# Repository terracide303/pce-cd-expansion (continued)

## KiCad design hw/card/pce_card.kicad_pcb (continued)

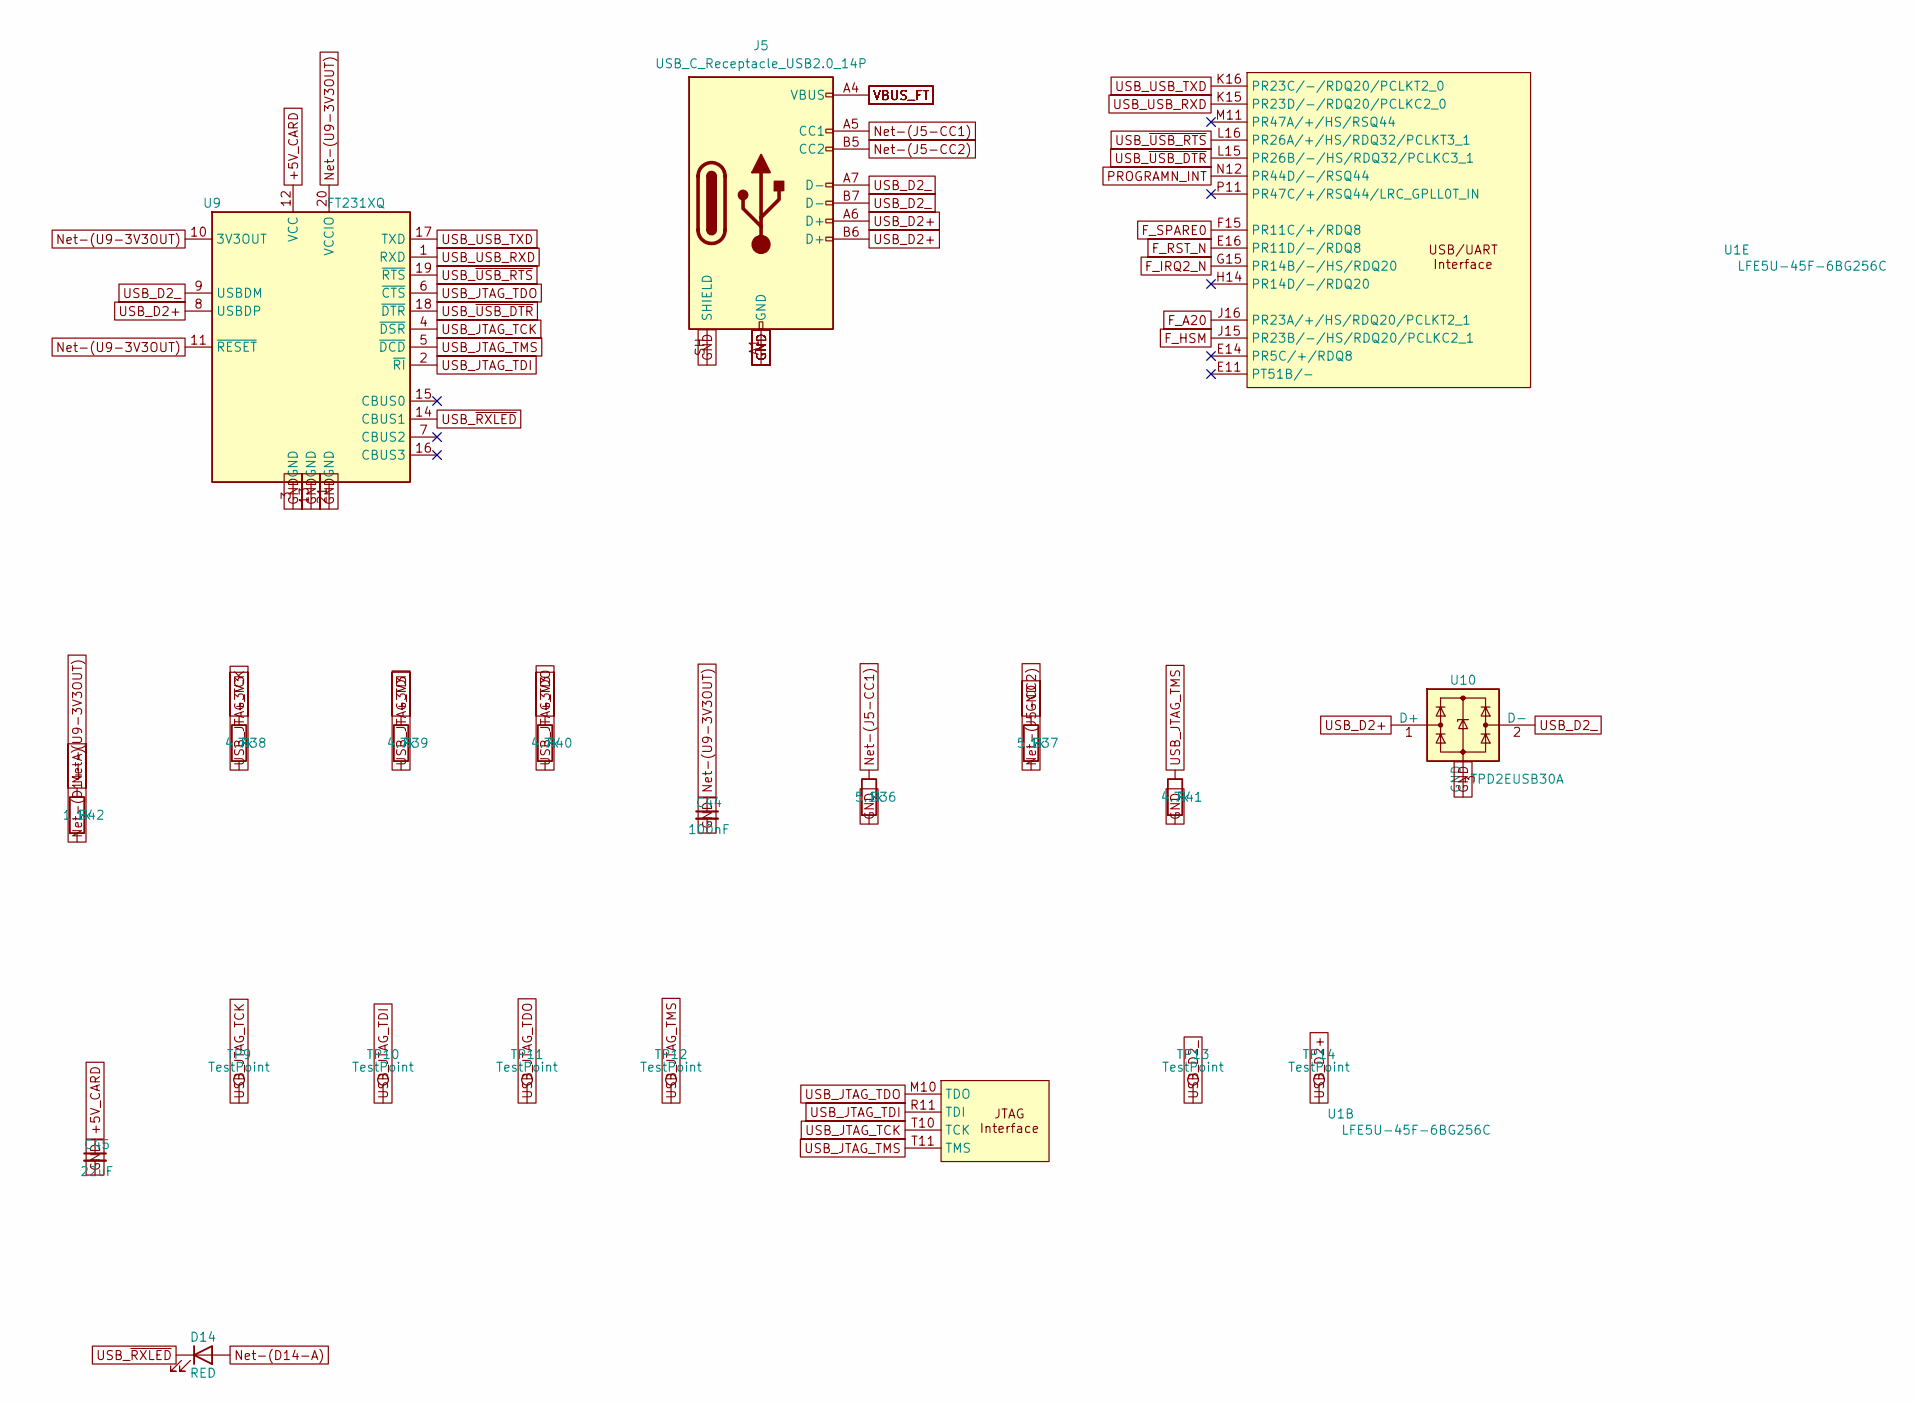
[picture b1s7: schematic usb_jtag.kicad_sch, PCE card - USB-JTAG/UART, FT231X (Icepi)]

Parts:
C44: 100nF; C_0402_1005Metric; LCSC C307331
C45: 22uF; C_0603_1608Metric; LCSC C59461
D14: RED; LED_0603_1608Metric; LCSC C2286
J5: USB_C_Receptacle_USB2.0_14P; USB_C_Receptacle_GCT_USB4105-xx-A_16P_TopMnt_Horizontal; LCSC C2765186
R36, R37: 5.1k; R_0402_1005Metric; LCSC C25905
R38, R39, R40, R41: 4.7k; R_0402_1005Metric; LCSC C25900
R42: 1.1k; R_0402_1005Metric; LCSC C140223
TP9, TP10, TP11, TP12: TestPoint; TestPoint_Pad_D1.0mm_Blank
TP13, TP14: TestPoint; TestPoint_Pad_D2.0mm_Blank
U1: LFE5U-45F-6BG256C; BGA-256_14.0x14.0mm_Layout16x16_P0.8mm_Ball0.45mm_Pad0.32mm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; LCSC C1550834
U9: FT231XQ; QFN-20-1EP_4x4mm_P0.5mm_EP2.5x2.5mm; LCSC C132159
U10: TPD2EUSB30A; Texas_DRT-3; LCSC C3011197

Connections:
+3V3: R38.1, R39.1, R40.1; also elsewhere on the board
+5V_CARD: C45.1, U9.12 (VCC); also elsewhere on the board
F_A20: U1.J16 (PR23A/+/HS/RDQ20/PCLKT2_1); also elsewhere on the board
F_HSM: U1.J15 (PR23B/-/HS/RDQ20/PCLKC2_1); also elsewhere on the board
F_IRQ2_N: U1.G15 (PR14B/-/HS/RDQ20); also elsewhere on the board
F_RST_N: U1.E16 (PR11D/-/RDQ8); also elsewhere on the board
F_SPARE0: U1.F15 (PR11C/+/RDQ8); also elsewhere on the board
GND: C44.2, C45.2, J5.A1 (GND), J5.A12 (GND), J5.B1 (GND), J5.B12 (GND), J5.SH (SHIELD), R36.2, R37.1, R41.2, U9.3 (GND), U9.13 (GND), U9.21 (GND), U10.3 (GND); also elsewhere on the board
unnamed: D14.2 (A), R42.2
unnamed: J5.A5 (CC1), R36.1
unnamed: J5.B5 (CC2), R37.2
unnamed: C44.1, R42.1, U9.10 (3V3OUT), U9.11 (~RESET), U9.20 (VCCIO)
PROGRAMN_INT: U1.N12 (PR44D/-/RSQ44); also elsewhere on the board
USB_D2+: J5.A6 (D+), J5.B6 (D+), TP14.1, U9.8 (USBDP), U10.1 (D+)
USB_D2_: J5.A7 (D-), J5.B7 (D-), TP13.1, U9.9 (USBDM), U10.2 (D-)
USB_JTAG_TCK: R38.2, TP9.1, U1.T10 (TCK), U9.4 (~DSR)
USB_JTAG_TDI: R39.2, TP10.1, U1.R11 (TDI), U9.2 (~RI)
USB_JTAG_TDO: R40.2, TP11.1, U1.M10 (TDO), U9.6 (~CTS)
USB_JTAG_TMS: R41.1, TP12.1, U1.T11 (TMS), U9.5 (~DCD)
USB_USB_RXD: U1.K15 (PR23D/-/RDQ20/PCLKC2_0), U9.1 (RXD)
USB_USB_TXD: U1.K16 (PR23C/-/RDQ20/PCLKT2_0), U9.17 (TXD)
USB_~RXLED: D14.1 (K), U9.14 (CBUS1)
USB_~USB_DTR: U1.L15 (PR26B/-/HS/RDQ32/PCLKC3_1), U9.18 (~DTR)
USB_~USB_RTS: U1.L16 (PR26A/+/HS/RDQ32/PCLKT3_1), U9.19 (~RTS)
VBUS_FT: J5.A4 (VBUS), J5.A9 (VBUS), J5.B4 (VBUS), J5.B9 (VBUS); also elsewhere on the board

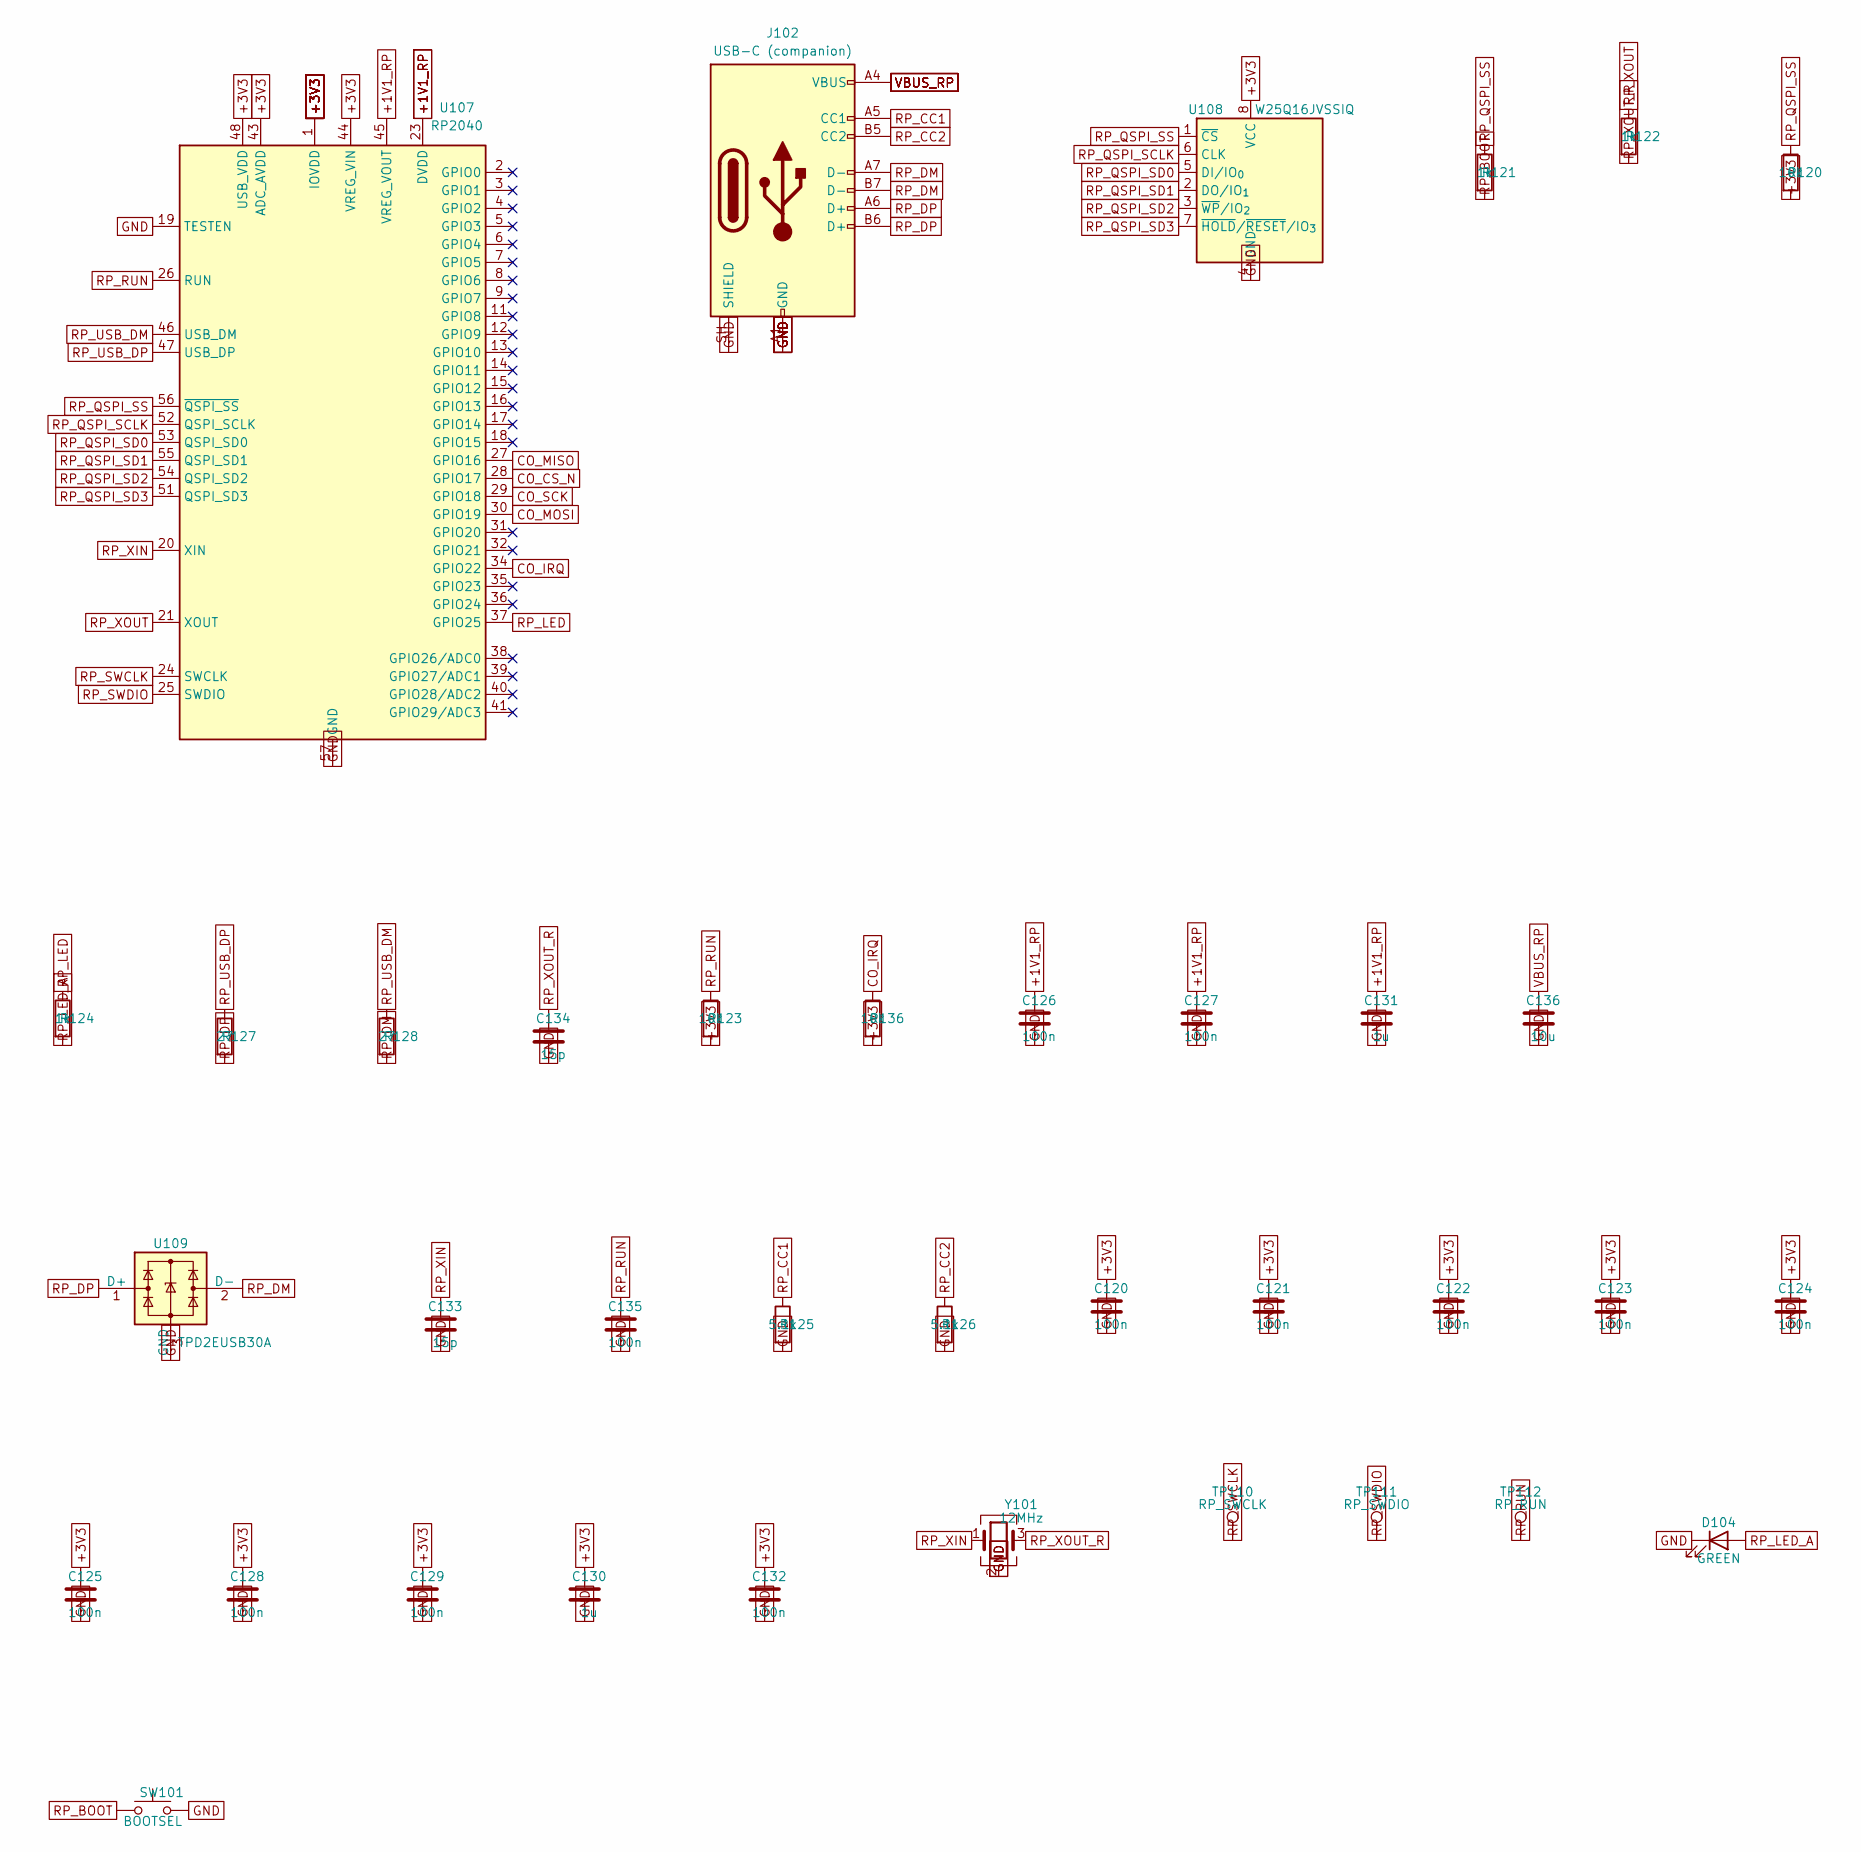
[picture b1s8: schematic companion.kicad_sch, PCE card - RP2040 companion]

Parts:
C120, C121, C122, C123, C124, C125, C126, C127, C128, C129, C132, C135: 100n; C_0402_1005Metric; LCSC C307331
C130, C131: 1u; C_0402_1005Metric
C133, C134: 15p; C_0402_1005Metric
C136: 10u; C_0603_1608Metric; LCSC C19702
D104: GREEN; LED_0603_1608Metric
J102: USB-C (companion); USB_C_Receptacle_GCT_USB4105-xx-A_16P_TopMnt_Horizontal; LCSC C2765186
R120, R123, R136: 10k; R_0402_1005Metric; LCSC C25744
R121, R122, R124: 1k; R_0402_1005Metric
R125, R126: 5.1k; R_0402_1005Metric; LCSC C25905
R127, R128: 27; R_0402_1005Metric
SW101: BOOTSEL; switch_button_TS-1088-AR02016; LCSC C720477
TP110: RP_SWCLK; TestPoint_Pad_D1.0mm
TP111: RP_SWDIO; TestPoint_Pad_D1.0mm
TP112: RP_RUN; TestPoint_Pad_D1.0mm
U107: RP2040; QFN-56-1EP_7x7mm_P0.4mm_EP3.2x3.2mm; LCSC C2040
U108: W25Q16JVSSIQ; SOIC-8_5.3x5.3mm_P1.27mm
U109: TPD2EUSB30A; Texas_DRT-3; LCSC C3011197
Y101: 12MHz; Crystal_SMD_3225-4Pin_3.2x2.5mm

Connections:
+1V1_RP: C126.1, C127.1, C131.1, U107.23 (DVDD), U107.45 (VREG_VOUT), U107.50 (DVDD)
+3V3: C120.1, C121.1, C122.1, C123.1, C124.1, C125.1, C128.1, C129.1, C130.1, C132.1, R120.2, R123.2, R136.2, U107.1 (IOVDD), U107.10 (IOVDD), U107.22 (IOVDD), U107.33 (IOVDD), U107.42 (IOVDD), U107.43 (ADC_AVDD), U107.44 (VREG_VIN), U107.48 (USB_VDD), U107.49 (IOVDD), U108.8 (VCC); also elsewhere on the board
CO_CS_N: U107.28 (GPIO17); also elsewhere on the board
CO_IRQ: R136.1, U107.34 (GPIO22); also elsewhere on the board
CO_MISO: U107.27 (GPIO16); also elsewhere on the board
CO_MOSI: U107.30 (GPIO19); also elsewhere on the board
CO_SCK: U107.29 (GPIO18); also elsewhere on the board
GND: C120.2, C121.2, C122.2, C123.2, C124.2, C125.2, C126.2, C127.2, C128.2, C129.2, C130.2, C131.2, C132.2, C133.2, C134.2, C135.2, C136.2, D104.1 (K), J102.A1 (GND), J102.A12 (GND), J102.B1 (GND), J102.B12 (GND), J102.SH (SHIELD), R125.2, R126.2, SW101.2, U107.19 (TESTEN), U107.57 (GND), U108.4 (GND), U109.3 (GND), Y101.2 (G), Y101.4 (G); also elsewhere on the board
RP_BOOT: R121.2, SW101.1
RP_CC1: J102.A5 (CC1), R125.1
RP_CC2: J102.B5 (CC2), R126.1
RP_DM: J102.A7 (D-), J102.B7 (D-), R128.2, U109.2 (D-)
RP_DP: J102.A6 (D+), J102.B6 (D+), R127.2, U109.1 (D+)
RP_LED: R124.1, U107.37 (GPIO25)
RP_LED_A: D104.2 (A), R124.2
RP_QSPI_SCLK: U107.52 (QSPI_SCLK), U108.6 (CLK)
RP_QSPI_SD0: U107.53 (QSPI_SD0), U108.5 (DI/IO_{0})
RP_QSPI_SD1: U107.55 (QSPI_SD1), U108.2 (DO/IO_{1})
RP_QSPI_SD2: U107.54 (QSPI_SD2), U108.3 (~WP/IO_{2})
RP_QSPI_SD3: U107.51 (QSPI_SD3), U108.7 (~HOLD/~RESET/IO_{3})
RP_QSPI_SS: R120.1, R121.1, U107.56 (~QSPI_SS), U108.1 (~CS)
RP_RUN: C135.1, R123.1, TP112.1, U107.26 (RUN)
RP_SWCLK: TP110.1, U107.24 (SWCLK)
RP_SWDIO: TP111.1, U107.25 (SWDIO)
RP_USB_DM: R128.1, U107.46 (USB_DM)
RP_USB_DP: R127.1, U107.47 (USB_DP)
RP_XIN: C133.1, U107.20 (XIN), Y101.1
RP_XOUT: R122.1, U107.21 (XOUT)
RP_XOUT_R: C134.1, R122.2, Y101.3
VBUS_RP: C136.1, J102.A4 (VBUS), J102.A9 (VBUS), J102.B4 (VBUS), J102.B9 (VBUS); also elsewhere on the board

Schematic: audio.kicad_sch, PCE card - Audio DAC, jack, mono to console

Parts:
C140, C141: 2.2u; C_0603_1608Metric
C142: 1u; C_0402_1005Metric
C143, C144, C145: 100n; C_0402_1005Metric; LCSC C307331
C146, C149, C150, C151: 10u; C_0603_1608Metric; LCSC C19702
C147, C148: 2.2n; C_0402_1005Metric
J103: 3.5 mm stereo; Jack_3.5mm_CUI_SJ-3523-SMT_Horizontal
R130, R134, R135: 10k; R_0402_1005Metric; LCSC C25744
R131, R132: 470; R_0402_1005Metric; LCSC C25117
R133: 4.7k; R_0402_1005Metric; LCSC C25900
U110: PCM5102APWR; TSSOP-20_4.4x6.5mm_P0.65mm

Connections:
+3V3: C143.1, C144.1, C145.1, C146.1, C150.1, C151.1, R130.2, U110.1 (CPVDD), U110.8 (AVDD), U110.20 (DVDD); also elsewhere on the board
AUD_L: C147.1, J103.T, R131.2, R134.1
AUD_MIX: C149.1, R133.1, R134.2, R135.2
AUD_R: C148.1, J103.R, R132.2, R135.1
BUS_AUDIO: C149.2; also elsewhere on the board
DAC_CAPM: C140.2, U110.4 (CAPM)
DAC_CAPP: C140.1, U110.2 (CAPP)
DAC_LDOO: C142.1, U110.18 (LDOO)
DAC_OUTL: R131.1, U110.6 (OUTL)
DAC_OUTR: R132.1, U110.7 (OUTR)
DAC_VNEG: C141.1, U110.5 (VNEG)
DAC_XSMT: R130.1, U110.17 (XSMT)
F_I2S_BCK: U110.13 (BCK); also elsewhere on the board
F_I2S_DIN: U110.14 (DIN); also elsewhere on the board
F_I2S_LRCK: U110.15 (LRCK); also elsewhere on the board
GND: C141.2, C142.2, C143.2, C144.2, C145.2, C146.2, C147.2, C148.2, C150.2, C151.2, J103.S, R133.2, U110.3 (CPGND), U110.9 (AGND), U110.10 (DEMP), U110.11 (FLT), U110.12 (SCK), U110.16 (FMT), U110.19 (DGND); also elsewhere on the board

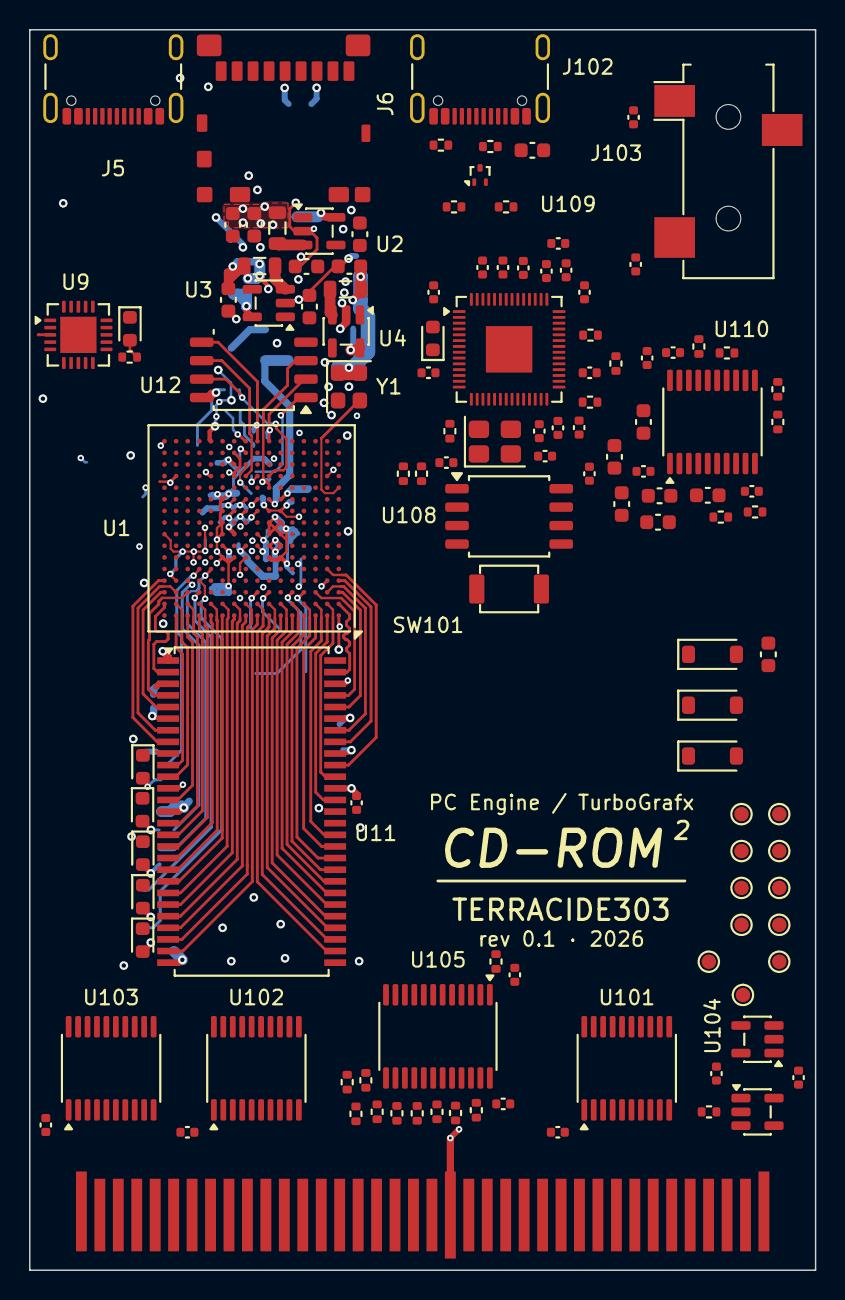
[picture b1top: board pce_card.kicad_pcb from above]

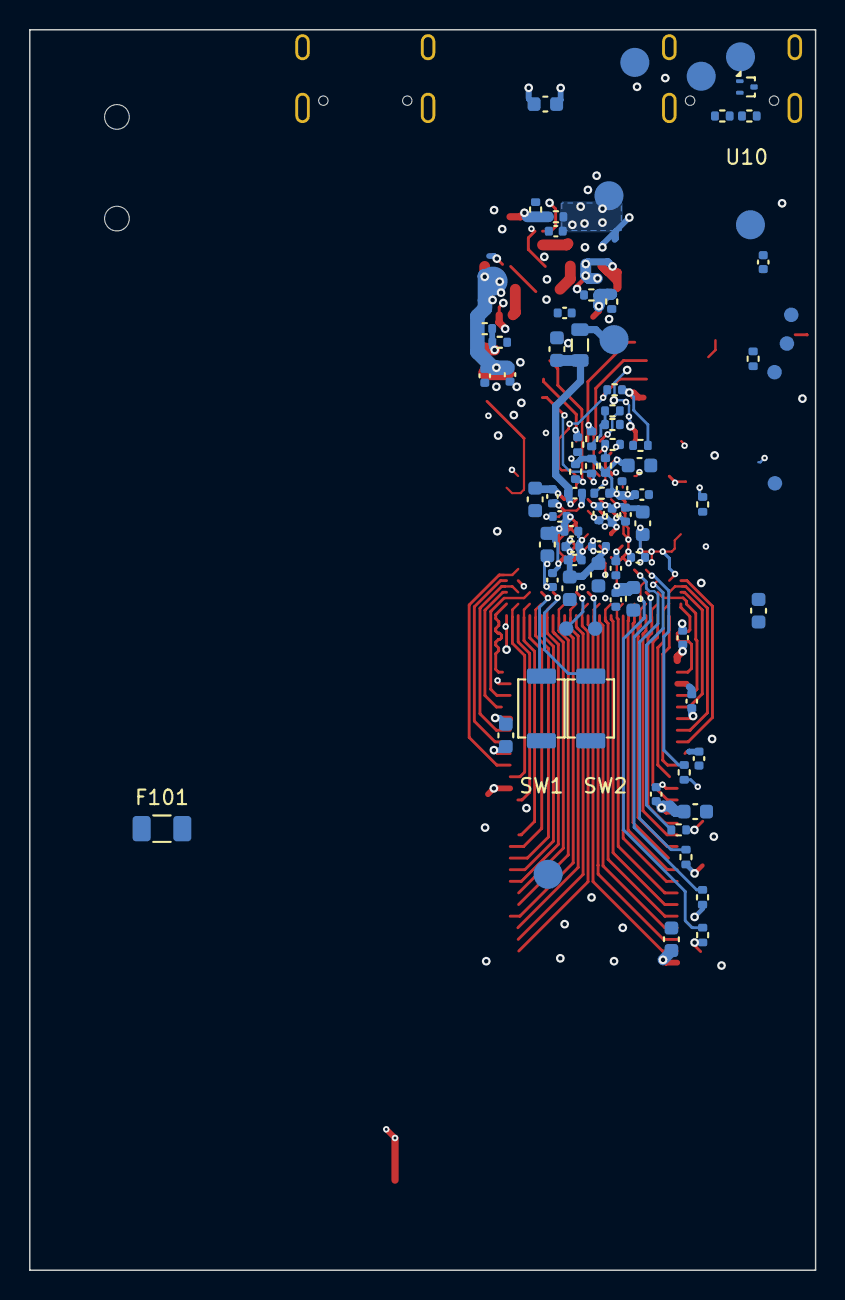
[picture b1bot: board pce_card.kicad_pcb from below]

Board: 4 copper layers, 54.1 x 85.4 mm, 205 parts (83 on the bottom side), 223 nets.

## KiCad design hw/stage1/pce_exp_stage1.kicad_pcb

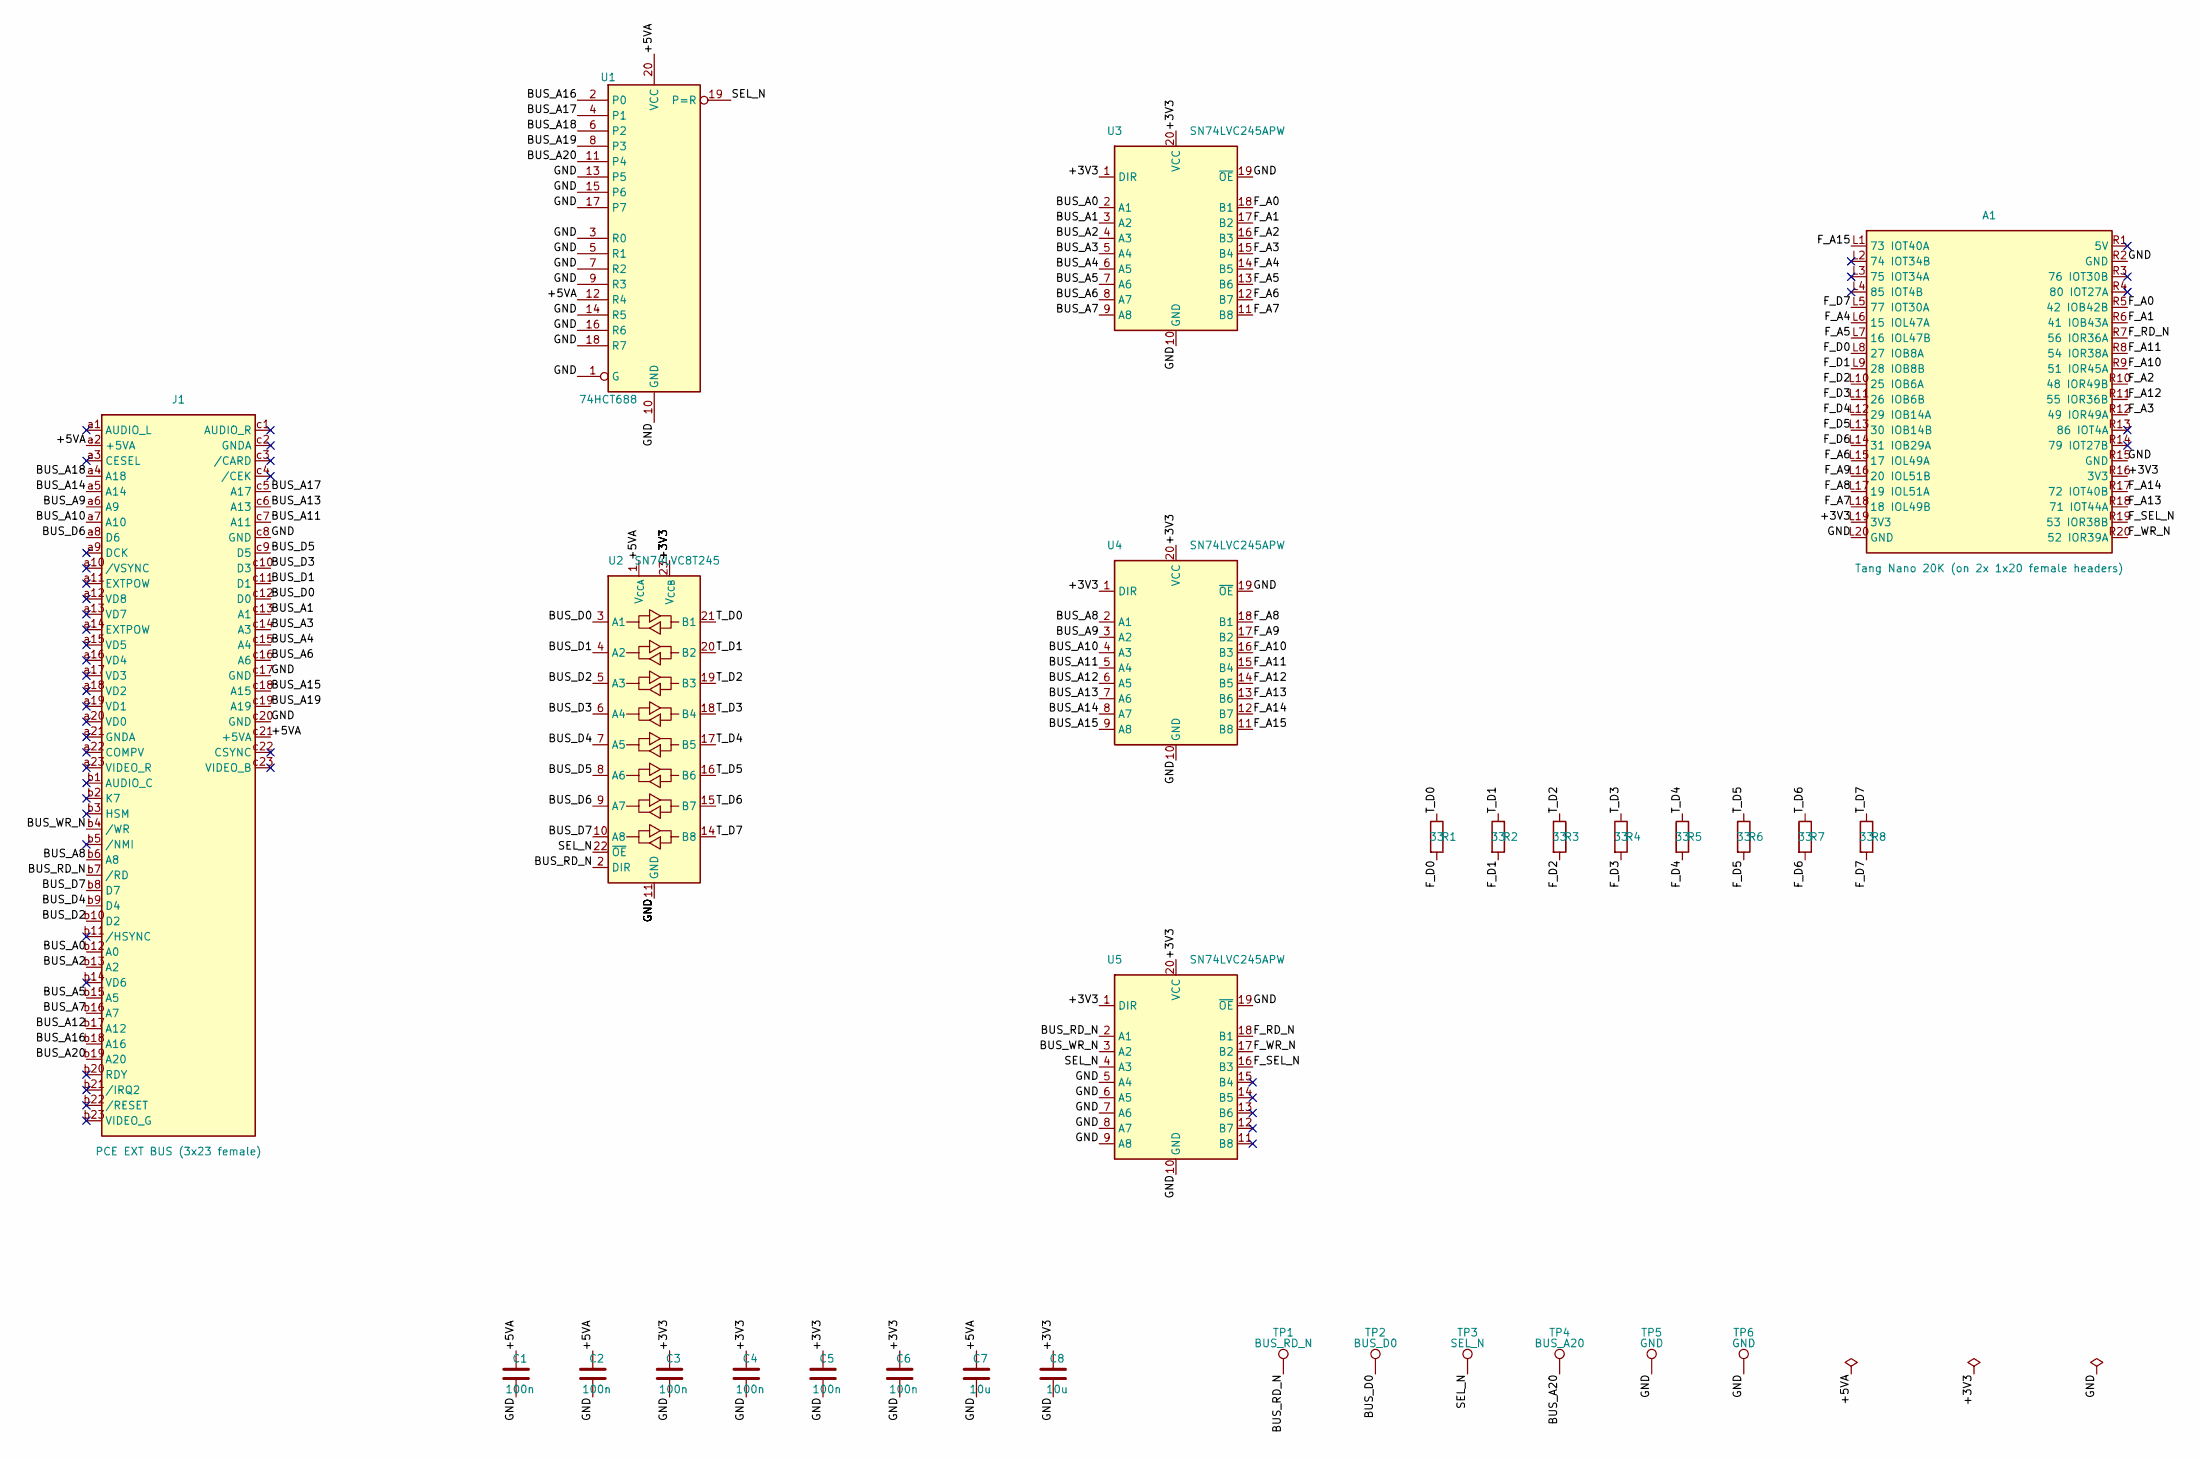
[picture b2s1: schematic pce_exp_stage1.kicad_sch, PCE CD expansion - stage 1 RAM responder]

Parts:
A1: Tang Nano 20K (on 2x 1x20 female headers); TangNano20K_Sockets
C1, C2, C3, C4, C5, C6: 100n; C_0603_1608Metric
C7, C8: 10u; C_0805_2012Metric
J1: PCE EXT BUS (3x23 female); PinSocket_3x23_P2.54mm_Vertical
R1, R2, R3, R4, R5, R6, R7, R8: 33; R_0603_1608Metric
TP1: BUS_RD_N; TestPoint_THTPad_D1.5mm_Drill0.7mm
TP2: BUS_D0; TestPoint_THTPad_D1.5mm_Drill0.7mm
TP3: SEL_N; TestPoint_THTPad_D1.5mm_Drill0.7mm
TP4: BUS_A20; TestPoint_THTPad_D1.5mm_Drill0.7mm
TP5, TP6: GND; TestPoint_THTPad_D1.5mm_Drill0.7mm
U1: 74HCT688; SOIC-20W_7.5x12.8mm_P1.27mm
U2: SN74LVC8T245; TSSOP-24_4.4x7.8mm_P0.65mm
U3, U4, U5: SN74LVC245APW; TSSOP-20_4.4x6.5mm_P0.65mm

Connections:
/+3V3: A1.L19 (3V3), A1.R16 (3V3), C3.1, C4.1, C5.1, C6.1, C8.1, U2.23 (V_{CCB}), U2.24 (V_{CCB}), U3.1 (DIR), U3.20 (VCC), U4.1 (DIR), U4.20 (VCC), U5.1 (DIR), U5.20 (VCC)
/+5VA: C1.1, C2.1, C7.1, J1.a2 (+5VA), J1.c21 (+5VA), U1.12 (R4), U1.20 (VCC), U2.1 (V_{CCA})
/BUS_A0: J1.b12 (A0), U3.2 (A1)
/BUS_A1: J1.c13 (A1), U3.3 (A2)
/BUS_A2: J1.b13 (A2), U3.4 (A3)
/BUS_A3: J1.c14 (A3), U3.5 (A4)
/BUS_A4: J1.c15 (A4), U3.6 (A5)
/BUS_A5: J1.b15 (A5), U3.7 (A6)
/BUS_A6: J1.c16 (A6), U3.8 (A7)
/BUS_A7: J1.b16 (A7), U3.9 (A8)
/BUS_A8: J1.b6 (A8), U4.2 (A1)
/BUS_A9: J1.a6 (A9), U4.3 (A2)
/BUS_A10: J1.a7 (A10), U4.4 (A3)
/BUS_A11: J1.c7 (A11), U4.5 (A4)
/BUS_A12: J1.b17 (A12), U4.6 (A5)
/BUS_A13: J1.c6 (A13), U4.7 (A6)
/BUS_A14: J1.a5 (A14), U4.8 (A7)
/BUS_A15: J1.c18 (A15), U4.9 (A8)
/BUS_A16: J1.b18 (A16), U1.2 (P0)
/BUS_A17: J1.c5 (A17), U1.4 (P1)
/BUS_A18: J1.a4 (A18), U1.6 (P2)
/BUS_A19: J1.c19 (A19), U1.8 (P3)
/BUS_A20: J1.b19 (A20), TP4.1, U1.11 (P4)
/BUS_D0: J1.c12 (D0), TP2.1, U2.3 (A1)
/BUS_D1: J1.c11 (D1), U2.4 (A2)
/BUS_D2: J1.b10 (D2), U2.5 (A3)
/BUS_D3: J1.c10 (D3), U2.6 (A4)
/BUS_D4: J1.b9 (D4), U2.7 (A5)
/BUS_D5: J1.c9 (D5), U2.8 (A6)
/BUS_D6: J1.a8 (D6), U2.9 (A7)
/BUS_D7: J1.b8 (D7), U2.10 (A8)
/BUS_RD_N: J1.b7 (/RD), TP1.1, U2.2 (DIR), U5.2 (A1)
/BUS_WR_N: J1.b4 (/WR), U5.3 (A2)
/F_A0: A1.R5 (42 IOB42B), U3.18 (B1)
/F_A1: A1.R6 (41 IOB43A), U3.17 (B2)
/F_A2: A1.R10 (48 IOR49B), U3.16 (B3)
/F_A3: A1.R12 (49 IOR49A), U3.15 (B4)
/F_A4: A1.L6 (15 IOL47A), U3.14 (B5)
/F_A5: A1.L7 (16 IOL47B), U3.13 (B6)
/F_A6: A1.L15 (17 IOL49A), U3.12 (B7)
/F_A7: A1.L18 (18 IOL49B), U3.11 (B8)
/F_A8: A1.L17 (19 IOL51A), U4.18 (B1)
/F_A9: A1.L16 (20 IOL51B), U4.17 (B2)
/F_A10: A1.R9 (51 IOR45A), U4.16 (B3)
/F_A11: A1.R8 (54 IOR38A), U4.15 (B4)
/F_A12: A1.R11 (55 IOR36B), U4.14 (B5)
/F_A13: A1.R18 (71 IOT44A), U4.13 (B6)
/F_A14: A1.R17 (72 IOT40B), U4.12 (B7)
/F_A15: A1.L1 (73 IOT40A), U4.11 (B8)
/F_D0: A1.L8 (27 IOB8A), R1.2
/F_D1: A1.L9 (28 IOB8B), R2.2
/F_D2: A1.L10 (25 IOB6A), R3.2
/F_D3: A1.L11 (26 IOB6B), R4.2
/F_D4: A1.L12 (29 IOB14A), R5.2
/F_D5: A1.L13 (30 IOB14B), R6.2
/F_D6: A1.L14 (31 IOB29A), R7.2
/F_D7: A1.L5 (77 IOT30A), R8.2
/F_RD_N: A1.R7 (56 IOR36A), U5.18 (B1)
/F_SEL_N: A1.R19 (53 IOR38B), U5.16 (B3)
/F_WR_N: A1.R20 (52 IOR39A), U5.17 (B2)
/GND: A1.L20 (GND), A1.R2 (GND), A1.R15 (GND), C1.2, C2.2, C3.2, C4.2, C5.2, C6.2, C7.2, C8.2, J1.c8 (GND), J1.c17 (GND), J1.c20 (GND), TP5.1, TP6.1, U1.1 (G), U1.3 (R0), U1.5 (R1), U1.7 (R2), U1.9 (R3), U1.10 (GND), U1.13 (P5), U1.14 (R5), U1.15 (P6), U1.16 (R6), U1.17 (P7), U1.18 (R7), U2.11 (GND), U2.12 (GND), U2.13 (GND), U3.10 (GND), U3.19 (~OE), U4.10 (GND), U4.19 (~OE), U5.5 (A4), U5.6 (A5), U5.7 (A6), U5.8 (A7), U5.9 (A8), U5.10 (GND), U5.19 (~OE)
/SEL_N: TP3.1, U1.19 (P=R), U2.22 (~OE), U5.4 (A3)
/T_D0: R1.1, U2.21 (B1)
/T_D1: R2.1, U2.20 (B2)
/T_D2: R3.1, U2.19 (B3)
/T_D3: R4.1, U2.18 (B4)
/T_D4: R5.1, U2.17 (B5)
/T_D5: R6.1, U2.16 (B6)
/T_D6: R7.1, U2.15 (B7)
/T_D7: R8.1, U2.14 (B8)

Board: 2 copper layers, 29 parts (0 on the bottom side), 70 nets, no tracks yet.

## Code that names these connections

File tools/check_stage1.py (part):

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    # The decoder: P=R low exactly for A20..A16 = 1 0000.
    for i, pin in enumerate(["2", "4", "6", "8", "11"]):
        check(on("U1", pin) == f"BUS_A{16 + i}", f"DECODE U1.{pin} (P{i}) must be BUS_A{16 + i}, is {on('U1', pin)}")
    for pin, want in [("3", "GND"), ("5", "GND"), ("7", "GND"), ("9", "GND"), ("12", "+5VA"), ("1", "GND"), ("19", "SEL_N")]:
        check(on("U1", pin) == want, f"DECODE U1.{pin} must be {want}, is {on('U1', pin)}")
    for p_, r_ in [("13", "14"), ("15", "16"), ("17", "18")]:
        check(on("U1", p_) == on("U1", r_), f"DECODE unused P/R pair U1.{p_}/{r_} must be equal")
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                a[k] = x

    cases = [
        ("two port pins swapped (A0 <-> A1)", lambda a: a.update({("J1", "b12"): "BUS_A1", ("J1", "c13"): "BUS_A0"})),
        ("two nets merged by touching pins (F_D0 + T_D1)", lambda a: merge(a, "F_D0", "T_D1")),
        ("data translator VCCA on 3.3 V", lambda a: a.update({("U2", "1"): "+3V3"})),
        ("an input translator turned round (DIR low)", lambda a: a.update({("U3", "1"): "GND"})),
        ("a 5 V bus line wired straight to the Tang", lambda a: a.update({("A1", "R5"): "BUS_A0"})),
        ("a kept pin used (WS2812 pin 79)", lambda a: a.update({("A1", "R14"): "F_A0"})),
        ("the Tang's USB 5 V tied to +5VA", lambda a: a.update({("A1", "R1"): "+5VA"})),
        ("decoder looking at the wrong address line", lambda a: a.update({("U1", "11"): "BUS_A15"})),
        ("an unused translator input left floating", lambda a: a.update({("U5", "9"): None})),
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
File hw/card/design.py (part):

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}
# J5 (the FT231X USB-C) VBUS: on the Icepi it is +5V itself; on the card it is VBUS_FT,
# which reaches +5V_CARD through D102. Pin-level override, below.
PIN_OVERRIDE = {("J5", p): "VBUS_FT" for p in ("A4", "A9", "B4", "B9")}

# The FPGA balls whose Icepi function is gone (header GPIO, GPDI, soft-USB),
# and what they carry on the card. Banks from prjtrellis-db (docs/FPGA-ECP5.md);
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cap("C133", "15p", "RP_XIN", "companion")
cap("C134", "15p", "RP_XOUT_R", "companion")
res("R123", "10k", "RP_RUN", "+3V3", "companion")
res("R136", "10k", "CO_IRQ", "+3V3", "companion")         # IRQ idle high while the FPGA is unconfigured (its pins pull down then)
cap("C135", "100n", "RP_RUN", "companion")
res("R124", "1k", "RP_LED", "RP_LED_A", "companion")         # GPIO25: the firmware's status LED
part("D104", "Device:LED", "GREEN", "LED_SMD:LED_0603_1608Metric", "companion", {"1": "GND", "2": "RP_LED_A"},
     )
for ref, net in [("TP110", "RP_SWCLK"), ("TP111", "RP_SWDIO"), ("TP112", "RP_RUN")]:
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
